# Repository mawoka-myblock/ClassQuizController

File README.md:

# ClassQuizController
Use a microcontroller (the ESP32) to play ClassQuiz with physical buttons! This repo includes the platformio code under `src/` and some other irrelevant files. Updates are pulled from the GitHub releases of this repository.

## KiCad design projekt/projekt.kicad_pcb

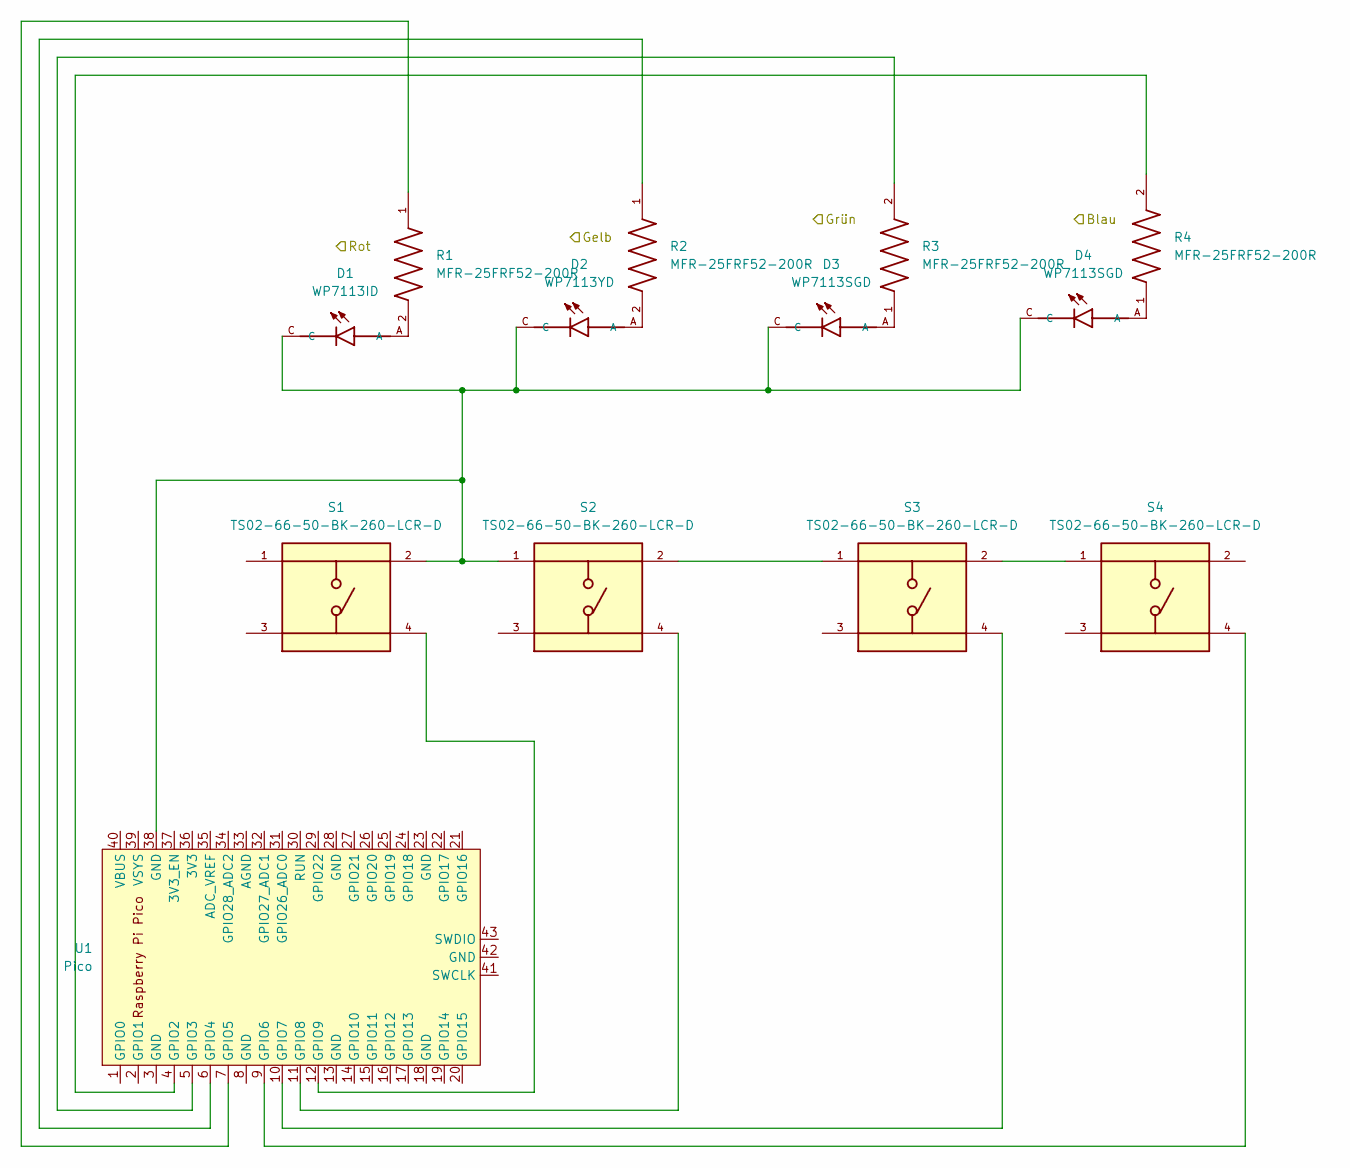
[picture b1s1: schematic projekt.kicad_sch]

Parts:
D1: WP7113ID; LED_WP7113ID
D2: WP7113YD; LED_WP7113YD
D3, D4: WP7113SGD; LED_WP7113SGD
R1, R2, R3, R4: MFR-25FRF52-200R; RESAD1100W55L680D260; PARTREV 201304
S1, S2, S3, S4: TS02-66-50-BK-260-LCR-D; SW_TS02-66-50-BK-260-LCR-D; PARTREV 1.0
U1: Pico; RPi_Pico_SMD_TH

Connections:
unnamed: D1.A, R1.2
unnamed: D1.C, D2.C, D3.C, D4.C, S1.2, S2.1, U1.38 (GND)
unnamed: D2.A, R2.2
unnamed: D3.A, R3.1
unnamed: D4.A, R4.1
unnamed: R1.1, U1.7 (GPIO5)
unnamed: R2.1, U1.6 (GPIO4)
unnamed: R3.2, U1.5 (GPIO3)
unnamed: R4.2, U1.4 (GPIO2)
unnamed: S1.4, U1.12 (GPIO9)
unnamed: S2.2, S3.1
unnamed: S2.4, U1.11 (GPIO8)
unnamed: S3.2, S4.1
unnamed: S3.4, U1.10 (GPIO7)
unnamed: S4.4, U1.9 (GPIO6)

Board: 2 copper layers, 12 parts (0 on the bottom side), 7 nets, no tracks yet.

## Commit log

2023-04-04 :sparkles: initial commit
2023-04-04 :page_facing_up: Added MPL-2.0
2023-04-04 [ImgBot] Optimize images
    /Sketch_Steckplatine.jpg -- 618.03kb -> 521.97kb (15.54%)
2023-04-15 :construction: Some progress
2023-06-29 Changes.
2023-06-30 Cleanup
2023-06-30 :bug: Fixed wrong URLs in code
